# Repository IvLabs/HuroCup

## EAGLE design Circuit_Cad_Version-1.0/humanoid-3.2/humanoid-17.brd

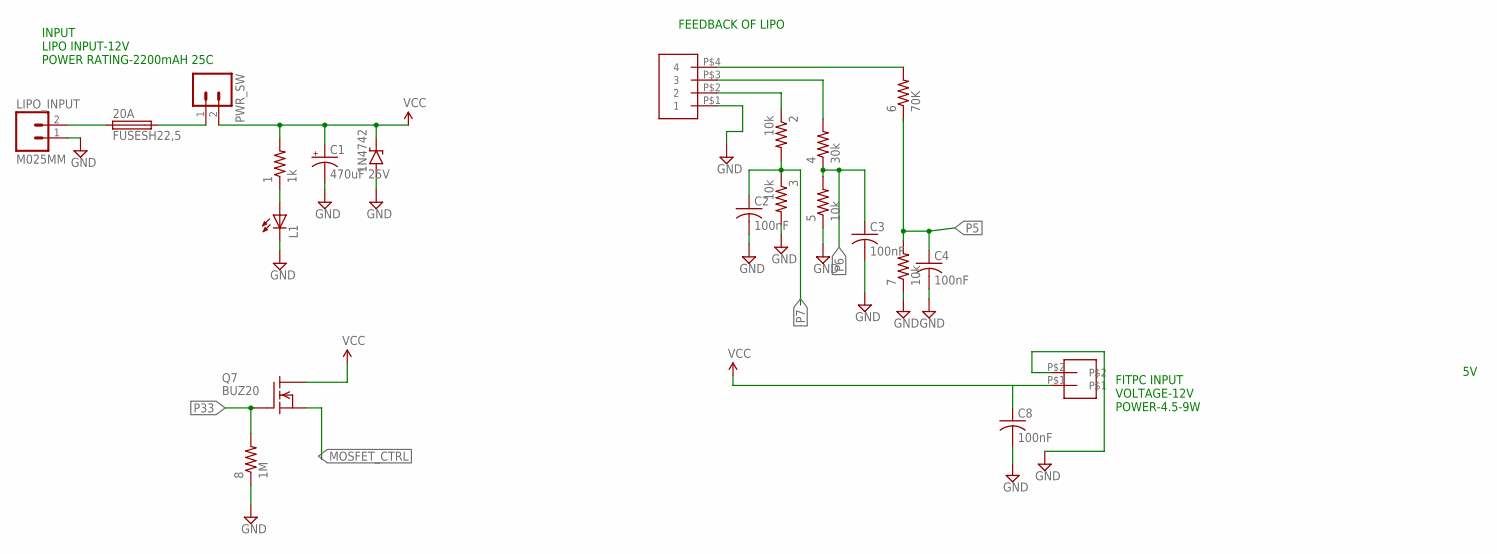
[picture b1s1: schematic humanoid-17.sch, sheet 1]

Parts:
1: 1k; R0805
1N4742: 1N47XX3; DO41-3
2, 3, 5, 7: 10k; R0805
4: 30k; R0805
6: 70K; R0805
8: 1M; R0805
20A: FUSESH22,5; SH22,5
C1: 470uF 25V; PANASONIC_G; PARTNO EEEFK1E471AP
C2, C3, C4, C8: 100nF; C1206; PARTNO C1206C104K5RACTU
FITPC: 2PINRIGHT
L1: LEDCHIPLED_1206; CHIPLED_1206
LIPO_INPUT: M025MM; SCREWTERMINAL-5MM-2
PWR_SW: M02PTH; 1X02
Q7: BUZ20; TO220
U$2: 4PINRIGHT

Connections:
GND: 1N4742.A, 3.2, 5.1, 7.1, 8.1, C1.-, C2.2, C3.2, C4.2, C8.2, FITPC.P$2, L1.C, LIPO_INPUT.1, U$2.P$1 (1); also elsewhere on the board
LIPO_FB4: 6.2, U$2.P$4 (4)
MOSFET_CTRL: Q7.3 (S); also elsewhere on the board
unnamed: 2.1, U$2.P$2 (2)
unnamed: 20A.2, PWR_SW.1
unnamed: 20A.1, LIPO_INPUT.2
unnamed: 4.2, U$2.P$3 (3)
unnamed: 1.1, L1.A
P5: 6.1, 7.2, C4.1; also elsewhere on the board
P6: 4.1, 5.2, C3.1; also elsewhere on the board
P7: 2.2, 3.1, C2.1; also elsewhere on the board
P33: 8.2, Q7.1 (G); also elsewhere on the board
VCC: 1.2, 1N4742.C, C1.+, C8.1, FITPC.P$1, PWR_SW.2, Q7.2 (D); also elsewhere on the board

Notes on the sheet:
INPUT LIPO INPUT-12V POWER RATING-2200mAH 25C
FITPC INPUT VOLTAGE-12V POWER-4.5-9W
FEEDBACK OF LIPO

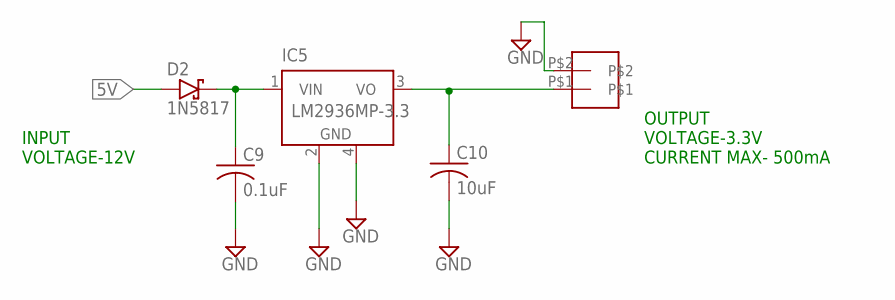
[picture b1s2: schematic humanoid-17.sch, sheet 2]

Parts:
3.3V1: 2PINRIGHT
C9: 0.1uF; C1206; PARTNO C1206C104K5RACTU
C10: 10uF; C1206; PARTNO C1206C104K5RACTU
D2: 1N5817; DO41-3
IC5: LM2936MP-3.3; SOT223

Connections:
3.3V: 3.3V1.P$1, C10.1, IC5.3 (VO); also elsewhere on the board
5V: D2.A; also elsewhere on the board
GND: 3.3V1.P$2, C9.2, C10.2, IC5.2 (GND), IC5.4 (GND); also elsewhere on the board
unnamed: C9.1, D2.C, IC5.1 (VIN)

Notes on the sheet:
INPUT VOLTAGE-12V
OUTPUT VOLTAGE-3.3V CURRENT MAX- 500mA

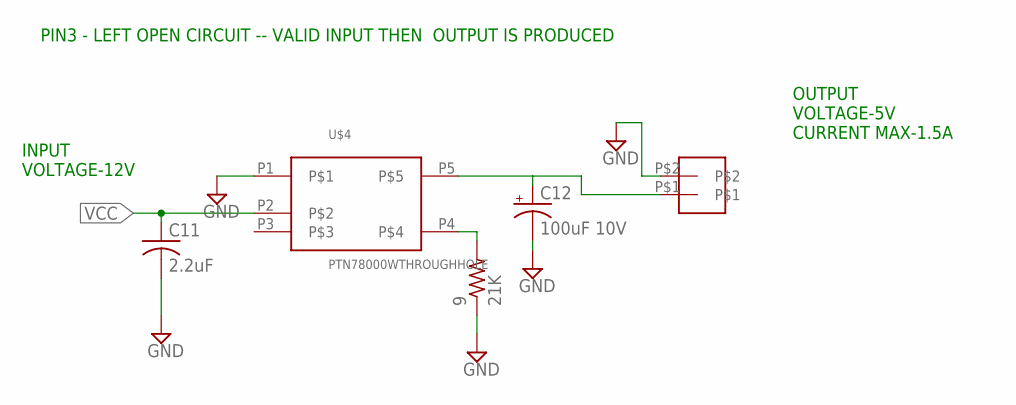
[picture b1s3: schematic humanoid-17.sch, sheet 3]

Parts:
5V1: 2PINRIGHT
9: 21K; R0805
C11: 2.2uF; C1206; MOUSER_PARTNO 810-C1608X7R1A225K
C12: 100uF 10V; PANASONIC_E; MOUSER_PARTNO 667-EEE-HA1A101P
U$4: PTN78000WTHROUGHHOLE; PTN78000W

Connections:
5V: 5V1.P$1, C12.+, U$4.P5; also elsewhere on the board
GND: 5V1.P$2, 9.1, C11.2, C12.-, U$4.P1; also elsewhere on the board
unnamed: 9.2, U$4.P4
VCC: C11.1, U$4.P2; also elsewhere on the board

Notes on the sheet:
INPUT VOLTAGE-12V
OUTPUT VOLTAGE-5V CURRENT MAX-1.5A
PIN3 - LEFT OPEN CIRCUIT -- VALID INPUT THEN OUTPUT IS PRODUCED

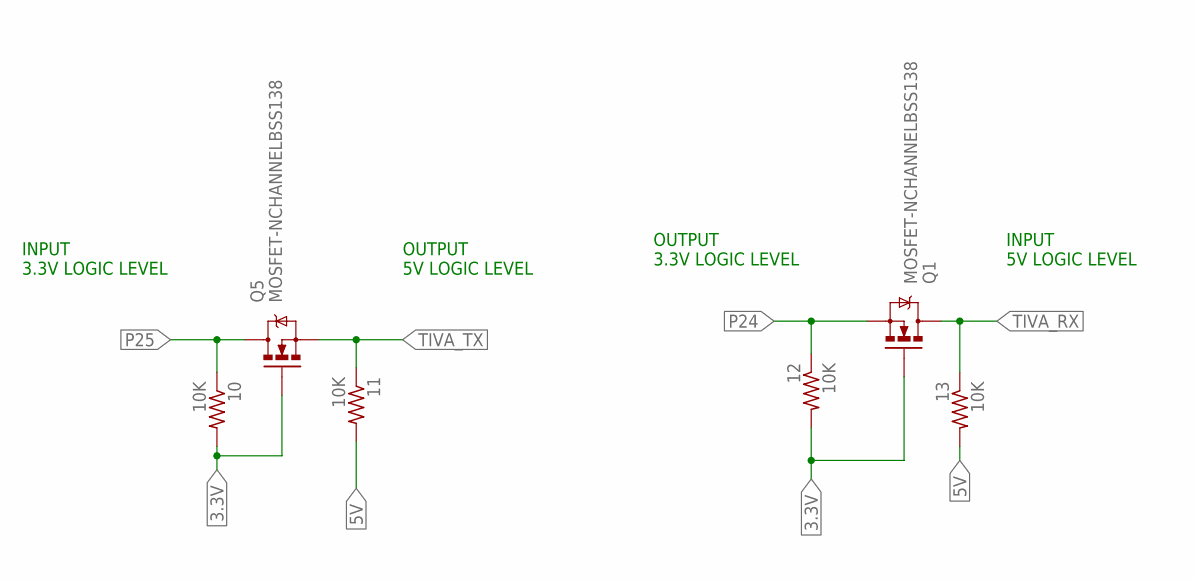
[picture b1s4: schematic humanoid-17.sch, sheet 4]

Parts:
10, 11, 12, 13: 10K; R0805
Q1, Q5: MOSFET-NCHANNELBSS138; SOT23

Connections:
3.3V: 10.2, 12.2, Q1.1 (G), Q5.1 (G); also elsewhere on the board
5V: 11.2, 13.2; also elsewhere on the board
P24: 12.1, Q1.2 (S); also elsewhere on the board
P25: 10.1, Q5.3 (D); also elsewhere on the board
TIVA_RX: 13.1, Q1.3 (D); also elsewhere on the board
TIVA_TX: 11.1, Q5.2 (S); also elsewhere on the board

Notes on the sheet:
INPUT 3.3V LOGIC LEVEL
OUTPUT 5V LOGIC LEVEL
OUTPUT 3.3V LOGIC LEVEL
INPUT 5V LOGIC LEVEL

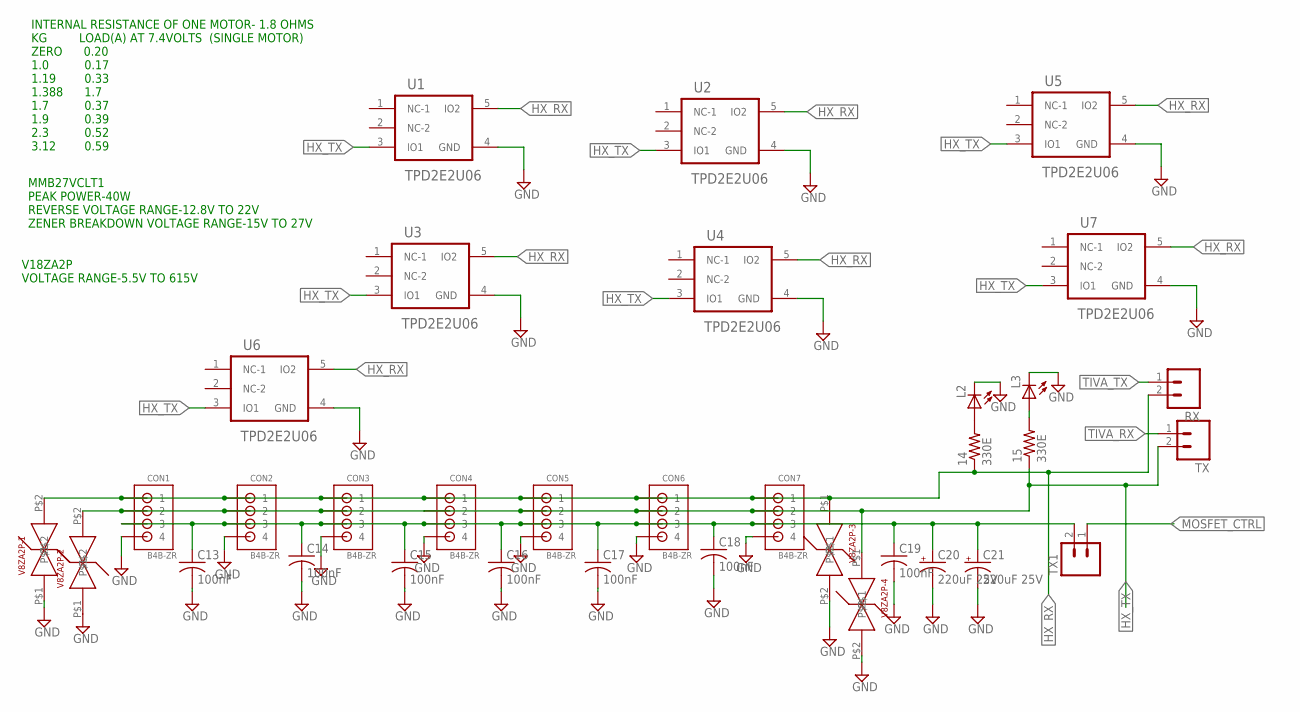
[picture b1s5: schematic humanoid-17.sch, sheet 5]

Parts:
14, 15: 330E; R0805
C13, C14, C15, C16, C17, C18, C19: 100nF; C1206; PARTNO C1206C104K5RACTU
C20, C21: 220uF 25V; PANASONIC_G; MOUSER_PARTNO 667-EEE-1EA221P
CON1, CON2, CON3, CON4, CON5, CON6, CON7: B4B-ZR; MPN B4B-ZR(LF)(SN)
L2, L3: LEDCHIPLED_1206; CHIPLED_1206
RX: M02PTH; 1X02
TX, TX1: M02PTH; 1X02
U1, U2, U3, U4, U5, U6, U7: TPD2E2U06; SOT50P160X60-5N
V8ZA2P-1, V8ZA2P-2, V8ZA2P-3, V8ZA2P-4: V18ZA2P

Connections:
GND: C13.2, C14.2, C15.2, C16.2, C17.2, C18.2, C19.2, C20.-, C21.-, CON1.4, CON2.4, CON3.4, CON4.4, CON5.4, CON6.4, CON7.4, L2.C, L3.C, U1.4 (GND), U2.4 (GND), U3.4 (GND), U4.4 (GND), U5.4 (GND), U6.4 (GND), U7.4 (GND), V8ZA2P-1.P$1, V8ZA2P-2.P$1, V8ZA2P-3.P$2, V8ZA2P-4.P$2; also elsewhere on the board
HX_RX: 14.1, CON1.1, CON2.1, CON3.1, CON4.1, CON5.1, CON6.1, CON7.1, RX.2, U1.5 (IO2), U2.5 (IO2), U3.5 (IO2), U4.5 (IO2), U5.5 (IO2), U6.5 (IO2), U7.5 (IO2), V8ZA2P-1.P$2, V8ZA2P-3.P$1; also elsewhere on the board
HX_TX: 15.1, CON1.2, CON2.2, CON3.2, CON4.2, CON5.2, CON6.2, CON7.2, TX.2, U1.3 (IO1), U2.3 (IO1), U3.3 (IO1), U4.3 (IO1), U5.3 (IO1), U6.3 (IO1), U7.3 (IO1), V8ZA2P-2.P$2, V8ZA2P-4.P$1; also elsewhere on the board
MOSFET_CTRL: TX1.1; also elsewhere on the board
MOSFET_CTRL1: C13.1, C14.1, C15.1, C16.1, C17.1, C18.1, C19.1, C20.+, C21.+, CON1.3, CON2.3, CON3.3, CON4.3, CON5.3, CON6.3, CON7.3, TX1.2
unnamed: 14.2, L2.A
unnamed: 15.2, L3.A
TIVA_RX: TX.1; also elsewhere on the board
TIVA_TX: RX.1; also elsewhere on the board

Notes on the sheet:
MMB27VCLT1 PEAK POWER-40W REVERSE VOLTAGE RANGE-12.8V TO 22V ZENER BREAKDOWN VOLTAGE RANGE-15V TO 27V
V18ZA2P VOLTAGE RANGE-5.5V TO 615V
INTERNAL RESISTANCE OF ONE MOTOR- 1.8 OHMS KG LOAD(A) AT 7.4VOLTS (SINGLE MOTOR) ZERO 0.20 1.0 0.17 1.19 0.33 1.388 1.7 1.7 0.37 1.9 0.39 2.3 0.52 3.12 0.59

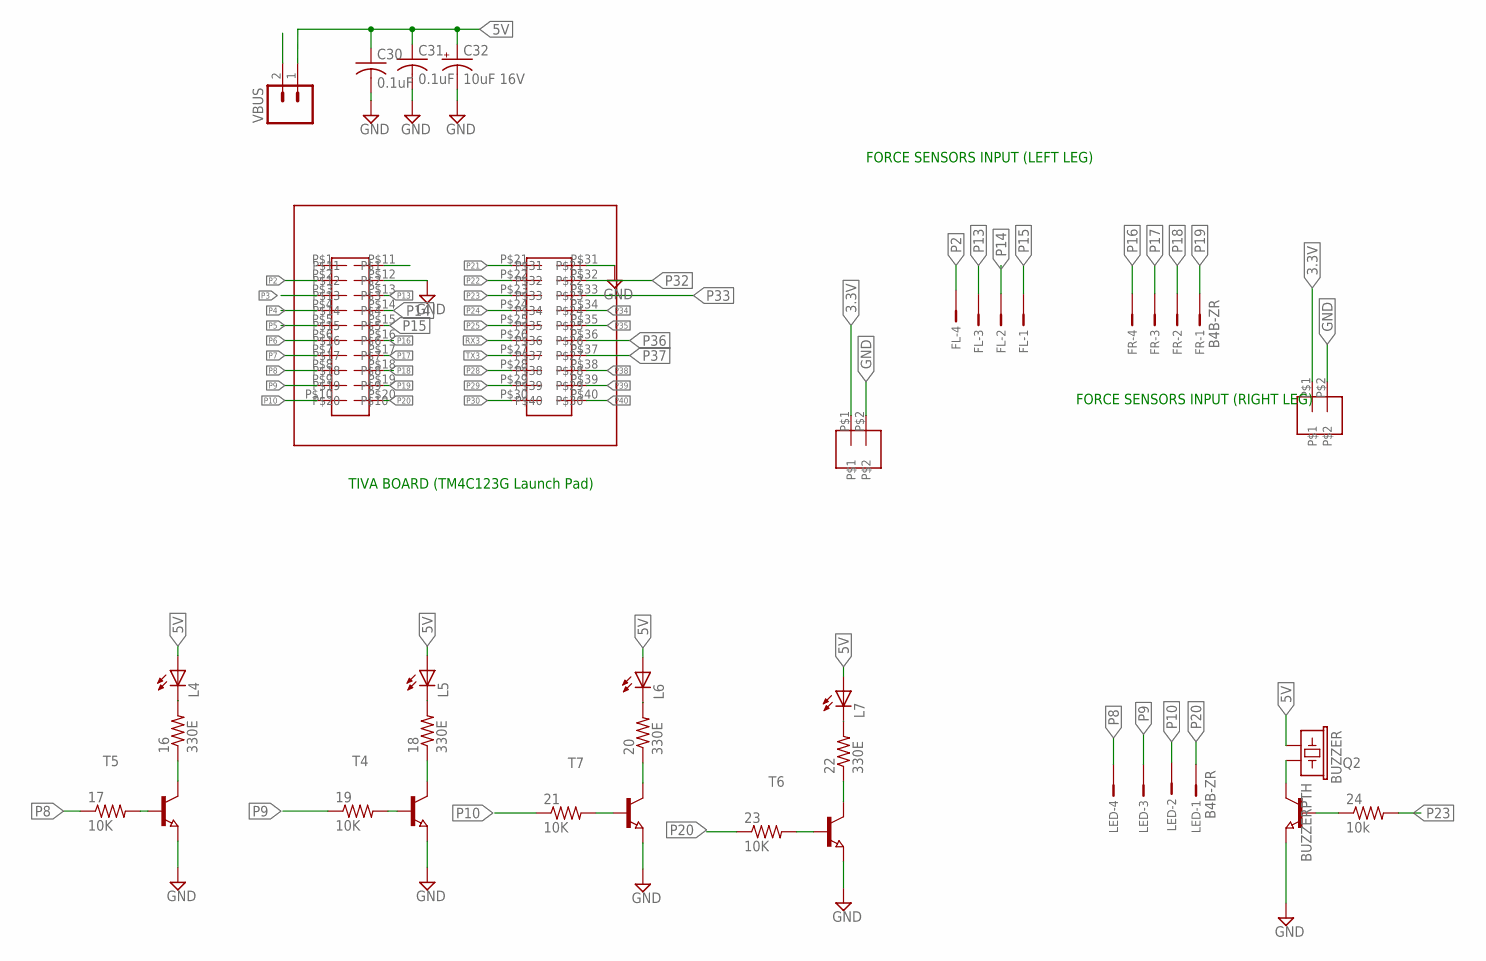
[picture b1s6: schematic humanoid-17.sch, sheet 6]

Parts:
3.3VL, 3.3VR: 2PINRIGHT
16, 18, 20, 22: 330E; R0805
17, 19, 21, 23: 10K; R0805
24: 10k; R0805
BUZZER: BUZZERPTH; BUZZER-12MM
C30, C31: 0.1uF; C1206
C32: 10uF 16V; PANASONIC_B
FL: B4B-ZR
FR: B4B-ZR
L4, L5, L6, L7: LEDCHIPLED_1206; CHIPLED_1206
LED: B4B-ZR
Q2: NPN-TRANSISTOR_SOT23; SOT23
T4, T5, T6, T7: NPN-TRANSISTOR_SOT23; SOT23
U$1: TIVA
VBUS: M02PTH; 1X02

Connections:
3.3V: 3.3VL.P$1, 3.3VR.P$1; also elsewhere on the board
5V: BUZZER.+ (1), C30.1, C31.1, C32.+, L4.A, L5.A, L6.A, L7.A, VBUS.1; also elsewhere on the board
5VJ: U$1.P$11, VBUS.2
GND: 3.3VL.P$2, 3.3VR.P$2, C30.2, C31.2, C32.-, Q2.2 (E), T4.2 (E), T5.2 (E), T6.2 (E), T7.2 (E), U$1.P$12, U$1.P$31; also elsewhere on the board
unnamed: BUZZER.- (2), Q2.3 (C)
unnamed: 24.1, Q2.1 (B)
unnamed: 19.2, T4.1 (B)
unnamed: 18.2, L5.C
unnamed: 18.1, T4.3 (C)
unnamed: 17.2, T5.1 (B)
unnamed: 16.2, L4.C
unnamed: 16.1, T5.3 (C)
unnamed: 23.2, T6.1 (B)
unnamed: 22.2, L7.C
unnamed: 22.1, T6.3 (C)
unnamed: 21.2, T7.1 (B)
unnamed: 20.2, L6.C
unnamed: 20.1, T7.3 (C)
P2: FL.4, U$1.P$2
P3: U$1.P$3; also elsewhere on the board
P4: U$1.P$4; also elsewhere on the board
P5: U$1.P$5; also elsewhere on the board
P6: U$1.P$6; also elsewhere on the board
P7: U$1.P$7; also elsewhere on the board
P8: 17.1, LED.4, U$1.P$8
P9: 19.1, LED.3, U$1.P$9
P10: 21.1, LED.2, U$1.P$10
P13: FL.3, U$1.P$13
P14: FL.2, U$1.P$14
P15: FL.1, U$1.P$15
P16: FR.4, U$1.P$16
P17: FR.3, U$1.P$17
P18: FR.2, U$1.P$18
P19: FR.1, U$1.P$19
P20: 23.1, LED.1, U$1.P$20
P21: U$1.P$21; also elsewhere on the board
P22: U$1.P$22; also elsewhere on the board
P23: 24.2, U$1.P$23; also elsewhere on the board
P24: U$1.P$24; also elsewhere on the board
P25: U$1.P$25; also elsewhere on the board
P28: U$1.P$28; also elsewhere on the board
P29: U$1.P$29; also elsewhere on the board
P30: U$1.P$30; also elsewhere on the board
P32: U$1.P$32; also elsewhere on the board
P33: U$1.P$33; also elsewhere on the board
P34: U$1.P$34; also elsewhere on the board
P35: U$1.P$35; also elsewhere on the board
P36: U$1.P$36; also elsewhere on the board
P37: U$1.P$37; also elsewhere on the board
P38: U$1.P$38; also elsewhere on the board
P39: U$1.P$39; also elsewhere on the board
P40: U$1.P$40; also elsewhere on the board
RX3: U$1.P$26; also elsewhere on the board
TX3: U$1.P$27; also elsewhere on the board

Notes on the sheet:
TIVA BOARD (TM4C123G Launch Pad)
FORCE SENSORS INPUT (LEFT LEG)
FORCE SENSORS INPUT (RIGHT LEG)

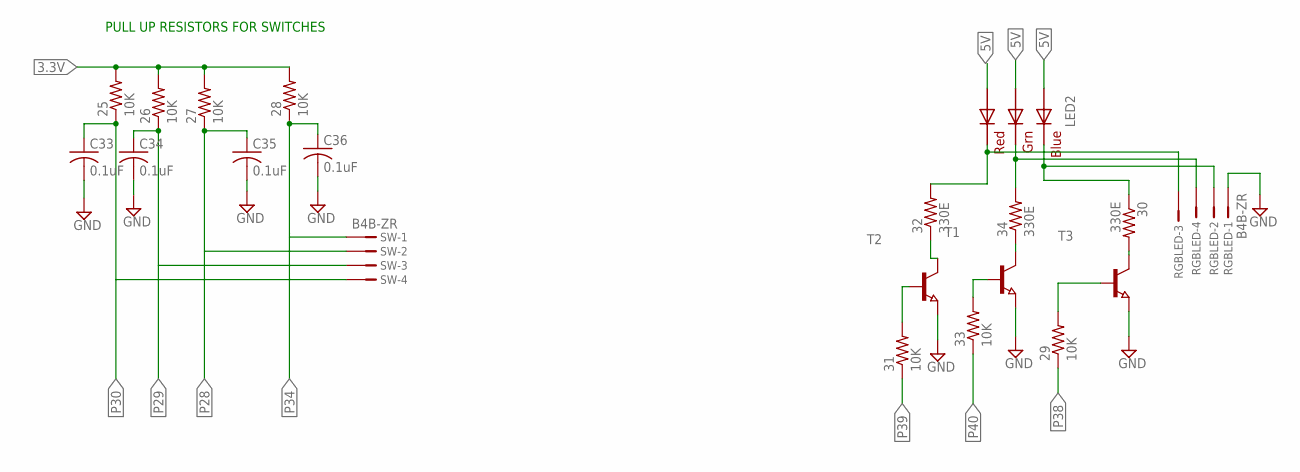
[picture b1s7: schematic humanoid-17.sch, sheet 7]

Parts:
25, 26, 27, 28, 29, 31, 33: 10K; R0805
30, 32, 34: 330E; R0805
C33, C34, C35, C36: 0.1uF; C1206; MOUSER_PARTNO 80-C0805C104M5R
LED2: RGBLED5050
RGBLED: B4B-ZR
SW: B4B-ZR
T1, T2, T3: NPN-TRANSISTOR_SOT23; SOT23

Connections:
3.3V: 25.2, 26.2, 27.2, 28.2; also elsewhere on the board
5V: LED2.1 (GREEN_A), LED2.2 (RED_A), LED2.3 (BLUE_A); also elsewhere on the board
GND: C33.2, C34.2, C35.2, C36.2, RGBLED.1, T1.2 (E), T2.2 (E), T3.2 (E); also elsewhere on the board
unnamed: 30.1, LED2.4 (BLUE_C), RGBLED.2
unnamed: 32.2, LED2.5 (RED_C), RGBLED.3
unnamed: 34.2, LED2.6 (GREEN_C), RGBLED.4
unnamed: 30.2, T3.3 (C)
unnamed: 32.1, T2.3 (C)
unnamed: 34.1, T1.3 (C)
unnamed: 29.2, T3.1 (B)
unnamed: 31.2, T2.1 (B)
unnamed: 33.2, T1.1 (B)
P28: 27.1, C35.1, SW.2; also elsewhere on the board
P29: 26.1, C34.1, SW.3; also elsewhere on the board
P30: 25.1, C33.1, SW.4; also elsewhere on the board
P34: 28.1, C36.1, SW.1; also elsewhere on the board
P38: 29.1; also elsewhere on the board
P39: 31.1; also elsewhere on the board
P40: 33.1; also elsewhere on the board

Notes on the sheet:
PULL UP RESISTORS FOR SWITCHES

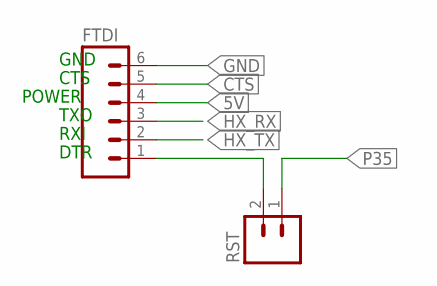
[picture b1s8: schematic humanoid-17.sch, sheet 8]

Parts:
FTDI: M06LOCK; 1X06_LOCK
RST: M02PTH; 1X02

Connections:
5V: FTDI.4; also elsewhere on the board
CTS: FTDI.5
GND: FTDI.6; also elsewhere on the board
HX_RX: FTDI.3; also elsewhere on the board
HX_TX: FTDI.2; also elsewhere on the board
unnamed: FTDI.1, RST.2
P35: RST.1; also elsewhere on the board

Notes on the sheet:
GND
CTS
POWER
TXO
RXI
DTR

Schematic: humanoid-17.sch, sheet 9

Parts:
P3, P4, P21, P22, P23, P26, P27: M01PTH; 1X01

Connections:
P3: P3.1; also elsewhere on the board
P4: P4.1; also elsewhere on the board
P21: P21.1; also elsewhere on the board
P22: P22.1; also elsewhere on the board
P23: P23.1; also elsewhere on the board
RX3: P26.1; also elsewhere on the board
TX3: P27.1; also elsewhere on the board

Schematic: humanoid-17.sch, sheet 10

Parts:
IMU: M081X08; 1X08

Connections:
3.3V: IMU.8; also elsewhere on the board
GND: IMU.7; also elsewhere on the board
P32: IMU.1; also elsewhere on the board
P36: IMU.5; also elsewhere on the board
P37: IMU.6; also elsewhere on the board

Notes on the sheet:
P1-INT P2-AD0 P3-ECL P4-EDA P5-SDA P6-SCL P7-GND P8-VCC
TIVA PINS P32-SCL(0) P36-SDA(3) P37-SCL(3)
IMU -0.8 * 0.6 (INCH) PLACE AT (62.34,42.38) THE ORIGIN OF FEMALE HEADERS

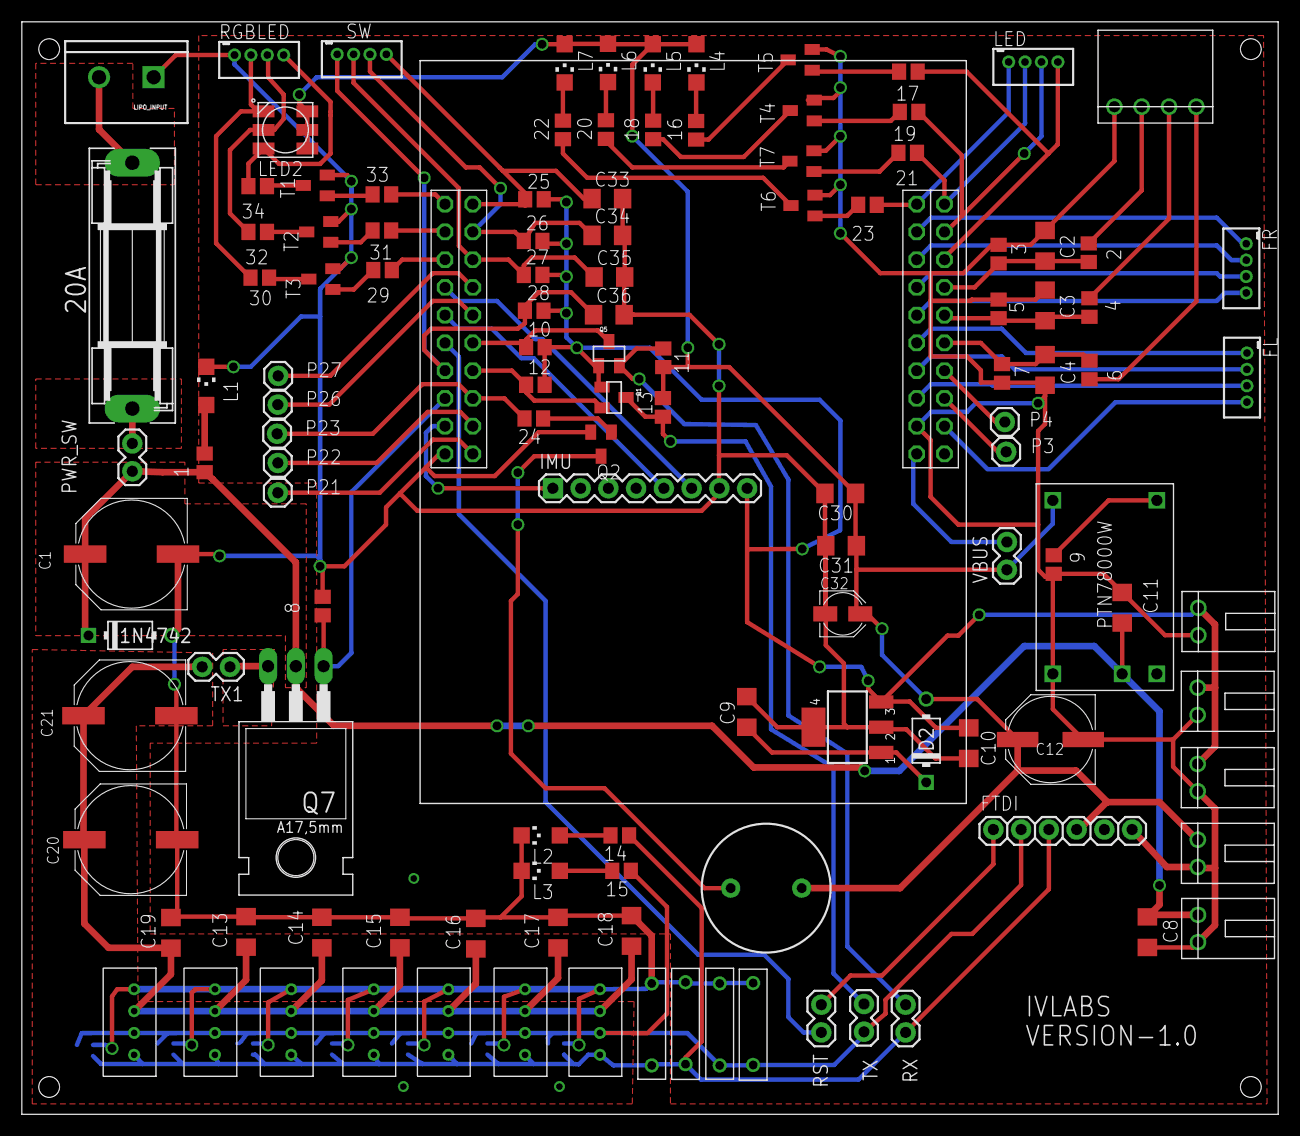
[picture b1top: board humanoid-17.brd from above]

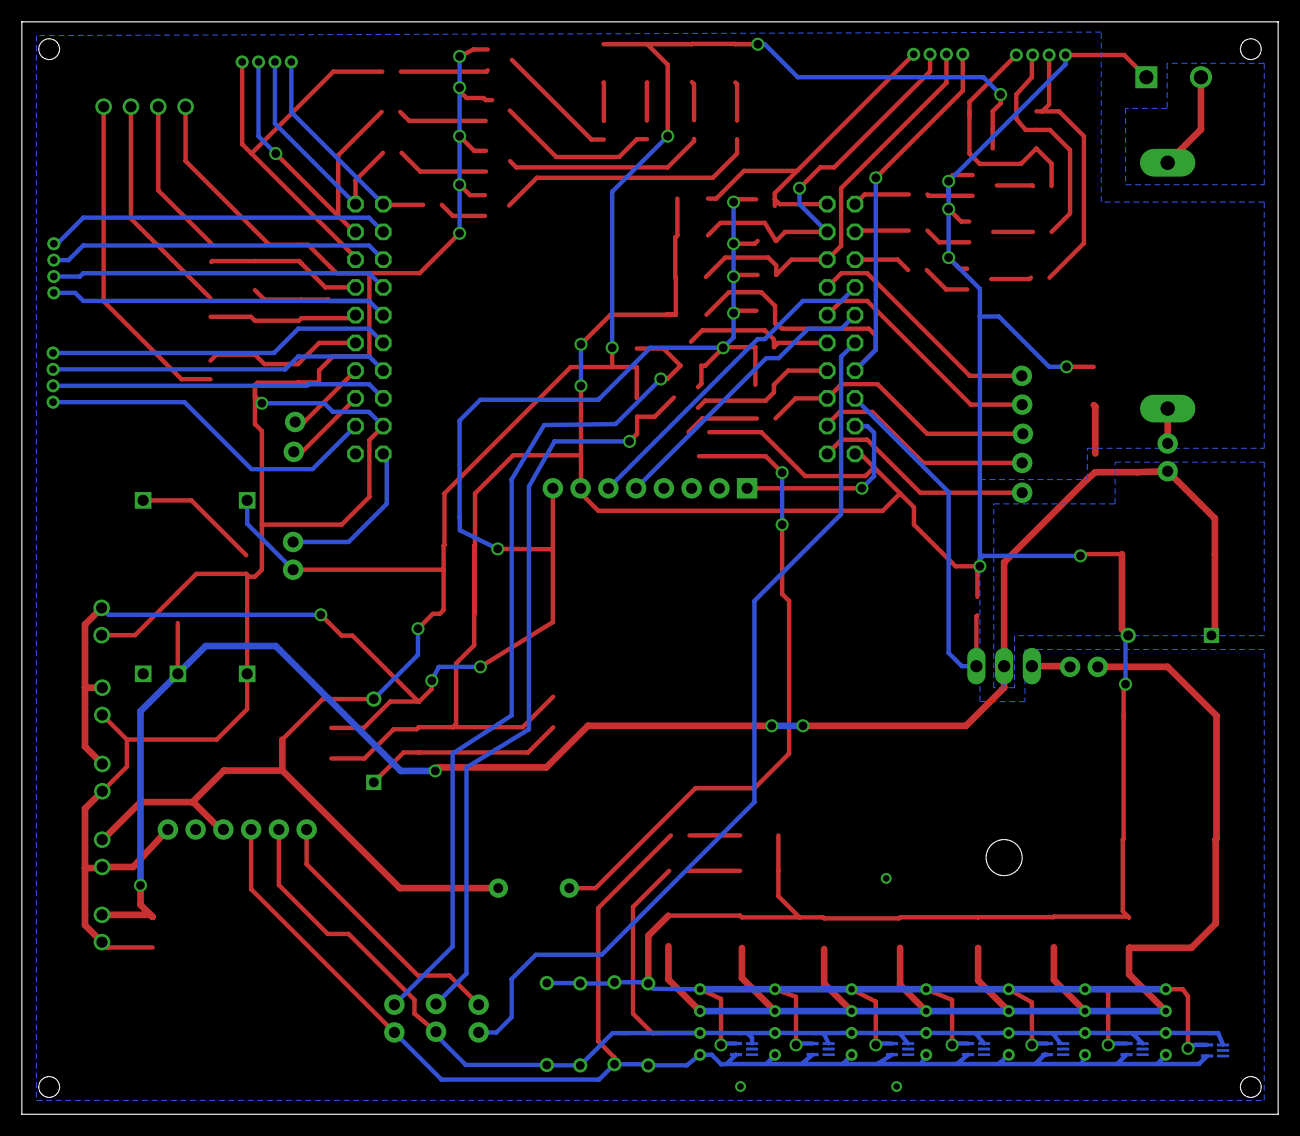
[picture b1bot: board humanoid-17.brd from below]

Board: 2 copper layers, 115.0 x 100.0 mm, 130 parts (7 on the bottom side), 81 nets.

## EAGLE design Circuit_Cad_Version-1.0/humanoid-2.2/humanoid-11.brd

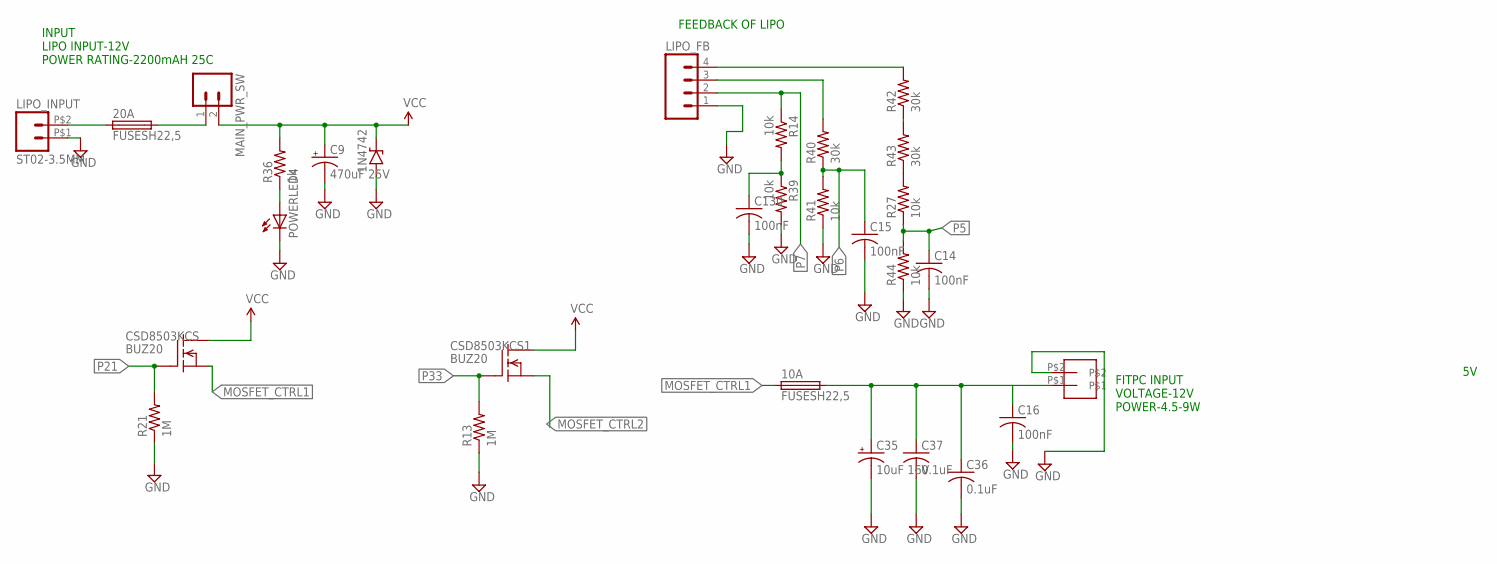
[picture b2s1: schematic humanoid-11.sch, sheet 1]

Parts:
1N4742: 1N47XX3; DO41-3
10A, 20A: FUSESH22,5; SH22,5
C9: 470uF 25V; PANASONIC_G; PARTNO EEEFK1E471AP
C14, C15, C16, C130: 100nF; C1206; PARTNO C1206C104K5RACTU
C35: 10uF 16V; PANASONIC_B
C36, C37: 0.1uF; C0805
CSD8503KCS, CSD8503KCS1: BUZ20; TO220
FITPC: 2PINRIGHT
LIPO_FB: M04PTH; 1X04
LIPO_INPUT: ST02-3.5MM; ED350V-02P
MAIN_PWR_SW: M02PTH; 1X02
POWERLED4: LEDCHIPLED_1206; CHIPLED_1206
R13, R21: 1M; R0805
R14, R27, R39, R41, R44: 10k; R0805
R36: 1k; R0805
R40, R42, R43: 30k; R0805

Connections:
GND: 1N4742.A, C9.-, C14.2, C15.2, C16.2, C35.-, C36.2, C37.2, C130.2, FITPC.P$2, LIPO_FB.1, LIPO_INPUT.P$1 (1), POWERLED4.C, R13.1, R21.1, R39.2, R41.1, R44.1; also elsewhere on the board
LIPO_FB4: LIPO_FB.4, R42.2
MOSFET_CTRL1: 10A.1, CSD8503KCS.3 (S)
MOSFET_CTRL2: CSD8503KCS1.3 (S); also elsewhere on the board
unnamed: C130.1, R14.2, R39.1
unnamed: 20A.2, MAIN_PWR_SW.1
unnamed: 20A.1, LIPO_INPUT.P$2 (2)
unnamed: R27.2, R43.1
unnamed: R42.1, R43.2
unnamed: LIPO_FB.3, R40.2
unnamed: 10A.2, C16.1, C35.+, C36.1, C37.1, FITPC.P$1
unnamed: POWERLED4.A, R36.1
P5: C14.1, R27.1, R44.2; also elsewhere on the board
P6: C15.1, R40.1, R41.2; also elsewhere on the board
P7: LIPO_FB.2, R14.1; also elsewhere on the board
P21: CSD8503KCS.1 (G), R21.2; also elsewhere on the board
P33: CSD8503KCS1.1 (G), R13.2; also elsewhere on the board
VCC: 1N4742.C, C9.+, CSD8503KCS.2 (D), CSD8503KCS1.2 (D), MAIN_PWR_SW.2, R36.2; also elsewhere on the board

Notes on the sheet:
INPUT LIPO INPUT-12V POWER RATING-2200mAH 25C
FITPC INPUT VOLTAGE-12V POWER-4.5-9W
FEEDBACK OF LIPO

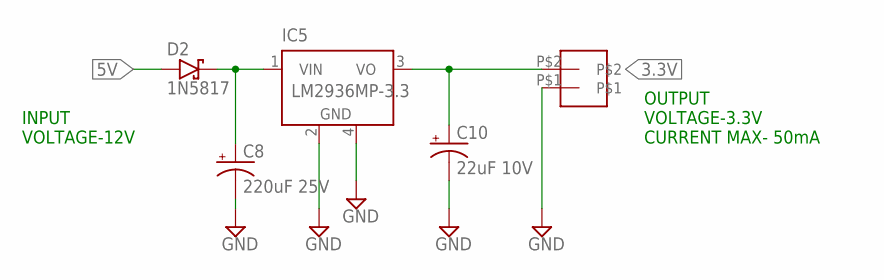
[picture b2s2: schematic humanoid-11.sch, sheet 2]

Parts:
3.3V1: 2PINRIGHT
C8: 220uF 25V; PANASONIC_G; MOUSER_PARTNO 667-EEE-1EA221P
C10: 22uF 10V; PANASONIC_B; PARTNO EEEFK1A220AR
D2: 1N5817; DO41-3
IC5: LM2936MP-3.3; SOT223

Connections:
3.3V: 3.3V1.P$2, C10.+, IC5.3 (VO); also elsewhere on the board
5V: D2.A; also elsewhere on the board
GND: 3.3V1.P$1, C8.-, C10.-, IC5.2 (GND), IC5.4 (GND); also elsewhere on the board
unnamed: C8.+, D2.C, IC5.1 (VIN)

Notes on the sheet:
INPUT VOLTAGE-12V
OUTPUT VOLTAGE-3.3V CURRENT MAX- 50mA

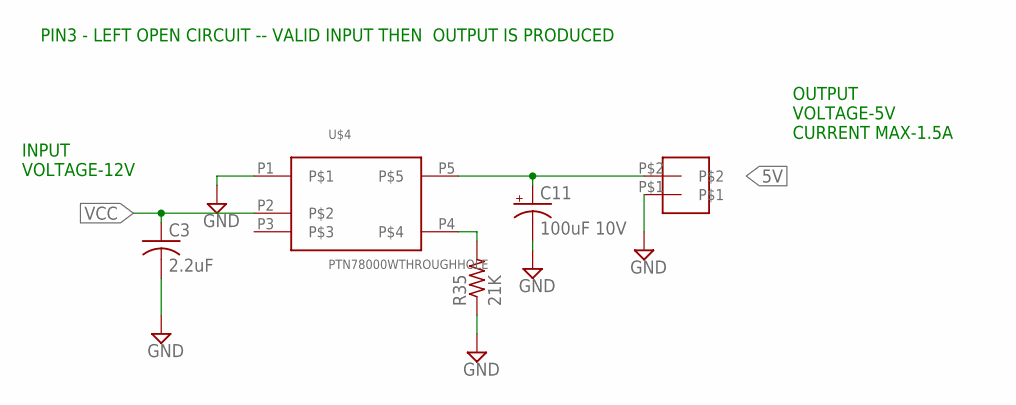
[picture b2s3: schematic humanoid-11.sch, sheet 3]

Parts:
5V1: 2PINRIGHT
C3: 2.2uF; C1608; MOUSER_PARTNO 810-C1608X7R1A225K
C11: 100uF 10V; PANASONIC_E; MOUSER_PARTNO 667-EEE-HA1A101P
R35: 21K; R0805
U$4: PTN78000WTHROUGHHOLE; PTN78000W

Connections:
5V: 5V1.P$2, C11.+, U$4.P5; also elsewhere on the board
GND: 5V1.P$1, C3.2, C11.-, R35.1, U$4.P1; also elsewhere on the board
unnamed: R35.2, U$4.P4
VCC: C3.1, U$4.P2; also elsewhere on the board

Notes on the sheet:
INPUT VOLTAGE-12V
OUTPUT VOLTAGE-5V CURRENT MAX-1.5A
PIN3 - LEFT OPEN CIRCUIT -- VALID INPUT THEN OUTPUT IS PRODUCED

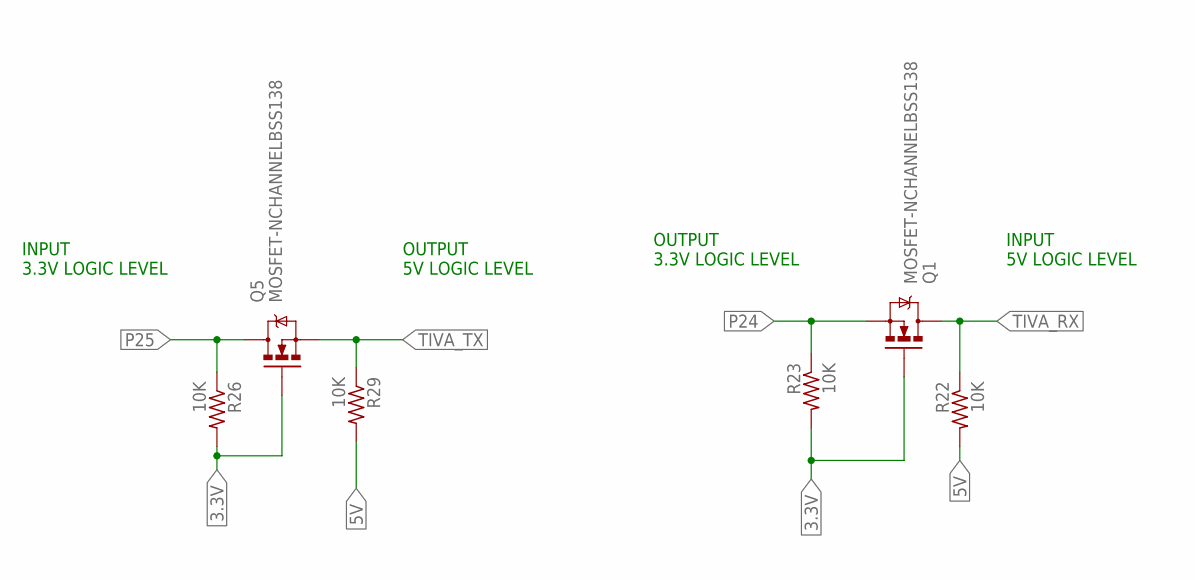
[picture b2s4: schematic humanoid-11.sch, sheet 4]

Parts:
Q1, Q5: MOSFET-NCHANNELBSS138; SOT23
R22, R23, R26, R29: 10K; R0805

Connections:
3.3V: Q1.1 (G), Q5.1 (G), R23.2, R26.2; also elsewhere on the board
5V: R22.2, R29.2; also elsewhere on the board
P24: Q1.2 (S), R23.1; also elsewhere on the board
P25: Q5.3 (D), R26.1; also elsewhere on the board
TIVA_RX: Q1.3 (D), R22.1; also elsewhere on the board
TIVA_TX: Q5.2 (S), R29.1; also elsewhere on the board

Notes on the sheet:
INPUT 3.3V LOGIC LEVEL
OUTPUT 5V LOGIC LEVEL
OUTPUT 3.3V LOGIC LEVEL
INPUT 5V LOGIC LEVEL

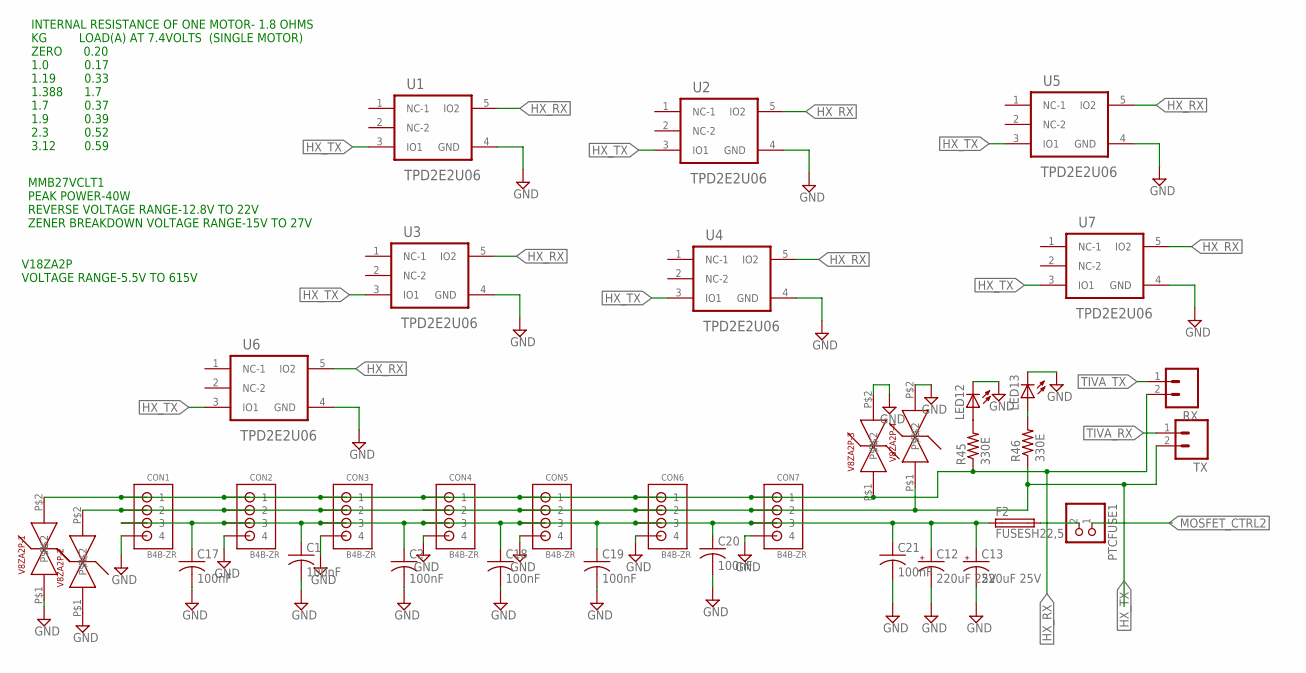
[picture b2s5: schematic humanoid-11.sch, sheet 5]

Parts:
C1, C2, C17, C18, C19, C20, C21: 100nF; C1206; PARTNO C1206C104K5RACTU
C12, C13: 220uF 25V; PANASONIC_G; MOUSER_PARTNO 667-EEE-1EA221P
CON1, CON2, CON3, CON4, CON5, CON6, CON7: B4B-ZR; MPN B4B-ZR(LF)(SN)
F2: FUSESH22,5; SH22,5
LED12, LED13: LEDCHIPLED_1206; CHIPLED_1206
PTCFUSE1: PINHD-1X2; 1X02
R45, R46: 330E; R0805
RX: M02PTH; 1X02
TX: M02PTH; 1X02
U1, U2, U3, U4, U5, U6, U7: TPD2E2U06; SOT50P160X60-5N
V8ZA2P-1, V8ZA2P-2, V8ZA2P-3, V8ZA2P-4: V18ZA2P

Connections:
GND: C1.2, C2.2, C12.-, C13.-, C17.2, C18.2, C19.2, C20.2, C21.2, CON1.4, CON2.4, CON3.4, CON4.4, CON5.4, CON6.4, CON7.4, LED12.C, LED13.C, U1.4 (GND), U2.4 (GND), U3.4 (GND), U4.4 (GND), U5.4 (GND), U6.4 (GND), U7.4 (GND), V8ZA2P-1.P$1, V8ZA2P-2.P$1, V8ZA2P-3.P$2, V8ZA2P-4.P$2; also elsewhere on the board
HX_RX: CON1.1, CON2.1, CON3.1, CON4.1, CON5.1, CON6.1, CON7.1, R45.1, RX.2, U1.5 (IO2), U2.5 (IO2), U3.5 (IO2), U4.5 (IO2), U5.5 (IO2), U6.5 (IO2), U7.5 (IO2), V8ZA2P-1.P$2, V8ZA2P-3.P$1; also elsewhere on the board
HX_TX: CON1.2, CON2.2, CON3.2, CON4.2, CON5.2, CON6.2, CON7.2, R46.1, TX.2, U1.3 (IO1), U2.3 (IO1), U3.3 (IO1), U4.3 (IO1), U5.3 (IO1), U6.3 (IO1), U7.3 (IO1), V8ZA2P-2.P$2, V8ZA2P-4.P$1; also elsewhere on the board
MOSFET_CTRL2: PTCFUSE1.1; also elsewhere on the board
unnamed: C1.1, C2.1, C12.+, C13.+, C17.1, C18.1, C19.1, C20.1, C21.1, CON1.3, CON2.3, CON3.3, CON4.3, CON5.3, CON6.3, CON7.3, F2.1
unnamed: F2.2, PTCFUSE1.2
unnamed: LED12.A, R45.2
unnamed: LED13.A, R46.2
TIVA_RX: TX.1; also elsewhere on the board
TIVA_TX: RX.1; also elsewhere on the board

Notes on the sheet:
MMB27VCLT1 PEAK POWER-40W REVERSE VOLTAGE RANGE-12.8V TO 22V ZENER BREAKDOWN VOLTAGE RANGE-15V TO 27V
V18ZA2P VOLTAGE RANGE-5.5V TO 615V
INTERNAL RESISTANCE OF ONE MOTOR- 1.8 OHMS KG LOAD(A) AT 7.4VOLTS (SINGLE MOTOR) ZERO 0.20 1.0 0.17 1.19 0.33 1.388 1.7 1.7 0.37 1.9 0.39 2.3 0.52 3.12 0.59

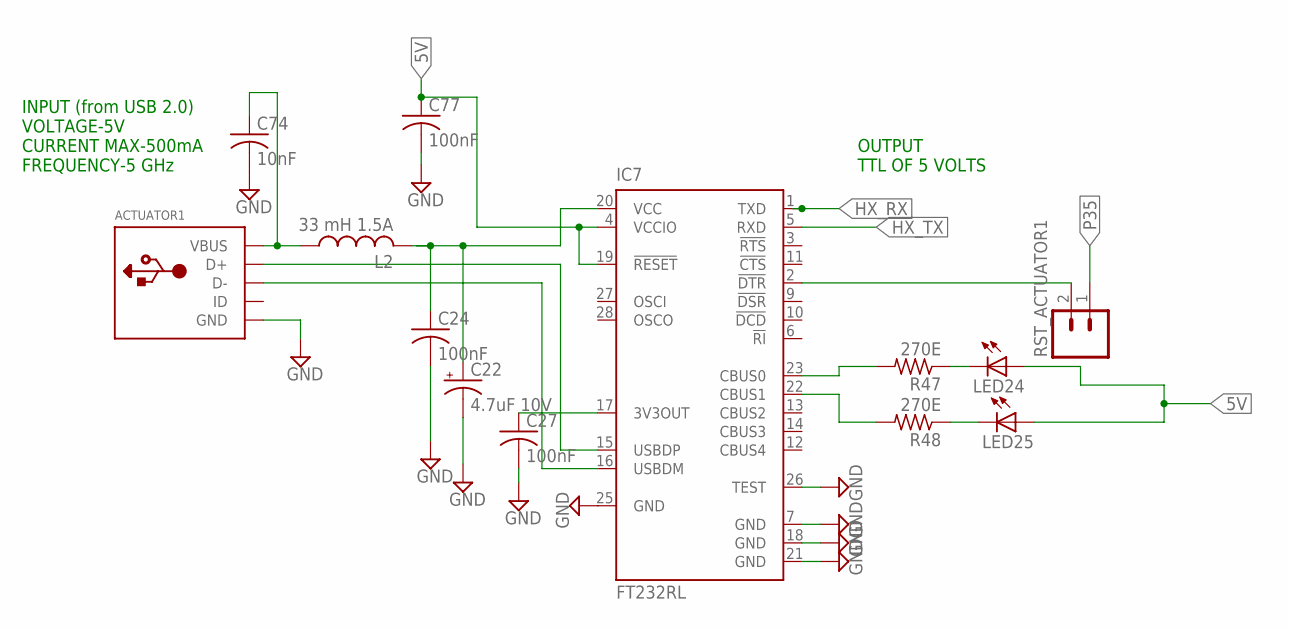
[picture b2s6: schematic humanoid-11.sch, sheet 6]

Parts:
ACTUATOR1: USBMINIB; USB-MINIB
C22: 4.7uF 10V; PANASONIC_B; MOUSER_PARTNO 667-10SVP4R7M
C24, C27: 100nF; C1206; PARTNO C1206C104K5RACTU
C74: 10nF; C1206
C77: 100nF; C1206
IC7: FT232RL; SSOP28
L2: 33 mH 1.5A; L0805; MOUSER_PARTNO 875-MI0805K400R-10
LED24, LED25: LEDCHIPLED_1206; CHIPLED_1206
R47, R48: 270E; R0805
RST_ACTUATOR1: M02PTH; 1X02

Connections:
5V: C77.1, IC7.4 (VCCIO), IC7.19 (!RESET), LED24.A, LED25.A; also elsewhere on the board
GND: ACTUATOR1.GND, C22.-, C24.2, C27.2, C74.2, C77.2, IC7.7 (GND), IC7.18 (GND), IC7.21 (GND), IC7.25 (GND), IC7.26 (TEST); also elsewhere on the board
HX_RX: IC7.1 (TXD); also elsewhere on the board
HX_TX: IC7.5 (RXD); also elsewhere on the board
unnamed: IC7.22 (CBUS1), R48.2
unnamed: IC7.23 (CBUS0), R47.2
unnamed: LED24.C, R47.1
unnamed: LED25.C, R48.1
unnamed: ACTUATOR1.VBUS, C74.1, L2.1
unnamed: C22.+, C24.1, IC7.20 (VCC), L2.2
unnamed: ACTUATOR1.D+, IC7.15 (USBDP)
unnamed: ACTUATOR1.D-, IC7.16 (USBDM)
unnamed: C27.1, IC7.17 (3V3OUT)
unnamed: IC7.2 (!DTR), RST_ACTUATOR1.2
P35: RST_ACTUATOR1.1; also elsewhere on the board

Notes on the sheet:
INPUT (from USB 2.0) VOLTAGE-5V CURRENT MAX-500mA FREQUENCY-5 GHz
OUTPUT TTL OF 5 VOLTS

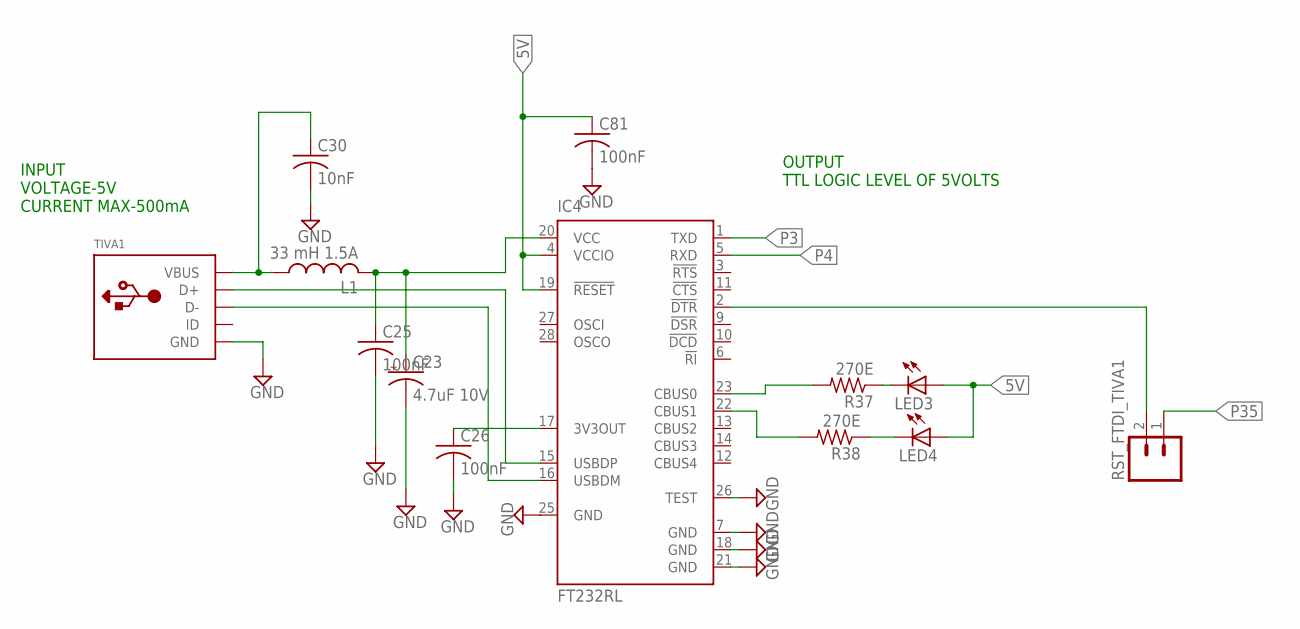
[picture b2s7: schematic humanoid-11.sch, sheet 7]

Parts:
C23: 4.7uF 10V; PANASONIC_B; MOUSER_PARTNO 667-10SVP4R7M
C25, C26: 100nF; C1206; PARTNO C1206C104K5RACTU
C30: 10nF; C1206
C81: 100nF; C1206
IC4: FT232RL; SSOP28
L1: 33 mH 1.5A; L0805; MOUSER_PARTNO 875-MI0805K400R-10
LED3, LED4: LEDCHIPLED_1206; CHIPLED_1206
R37, R38: 270E; R0805
RST_FTDI_TIVA1: M02PTH; 1X02
TIVA1: USBMINIB; USB-MINIB

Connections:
5V: C81.1, IC4.4 (VCCIO), IC4.19 (!RESET), LED3.A, LED4.A; also elsewhere on the board
GND: C23.-, C25.2, C26.2, C30.2, C81.2, IC4.7 (GND), IC4.18 (GND), IC4.21 (GND), IC4.25 (GND), IC4.26 (TEST), TIVA1.GND; also elsewhere on the board
unnamed: C30.1, L1.1, TIVA1.VBUS
unnamed: C23.+, C25.1, IC4.20 (VCC), L1.2
unnamed: IC4.15 (USBDP), TIVA1.D+
unnamed: IC4.16 (USBDM), TIVA1.D-
unnamed: LED3.C, R37.1
unnamed: LED4.C, R38.1
unnamed: IC4.23 (CBUS0), R37.2
unnamed: IC4.22 (CBUS1), R38.2
unnamed: C26.1, IC4.17 (3V3OUT)
unnamed: IC4.2 (!DTR), RST_FTDI_TIVA1.2
P3: IC4.1 (TXD); also elsewhere on the board
P4: IC4.5 (RXD); also elsewhere on the board
P35: RST_FTDI_TIVA1.1; also elsewhere on the board

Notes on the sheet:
INPUT VOLTAGE-5V CURRENT MAX-500mA
OUTPUT TTL LOGIC LEVEL OF 5VOLTS

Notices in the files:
parts and their libraries:
SparkFun-DiscreteSemi: Licensing: Creative Commons ShareAlike 4.0 International - https://creativecommons.org/licenses/by-sa/4.0
